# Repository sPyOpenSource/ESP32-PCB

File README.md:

# ESP32-PCBs

Those PCB boards are designed with ESP32. E,g, mini drone, rc car, solar controller, etc.

## Mini Drone Project

It has 4 Motor Controller for Mini Drone with Wireless Connections.

## RC Car Project

2 Motor Controller for RC Car with Wireless Connections. An RC car is a type of remote-controlled vehicle that can be driven by using a radio transmitter or a smartphone app. RC cars can have different sizes, shapes, designs, and features, depending on their purpose and performance. Some RC cars are made for racing, while others are made for off-road, drifting, crawling, or bashing.

## Solar Charger Project

It is the voltage regulator for solar panels for charging and output.

## Goals

The project aims to develop reusable ESP32 PCB designs for:
1. Robotics
2. RC vehicles
3. Drones
4. Solar energy systems
5. Embedded control
6. IoT applications

## License

See the individual project files and repository license for details.

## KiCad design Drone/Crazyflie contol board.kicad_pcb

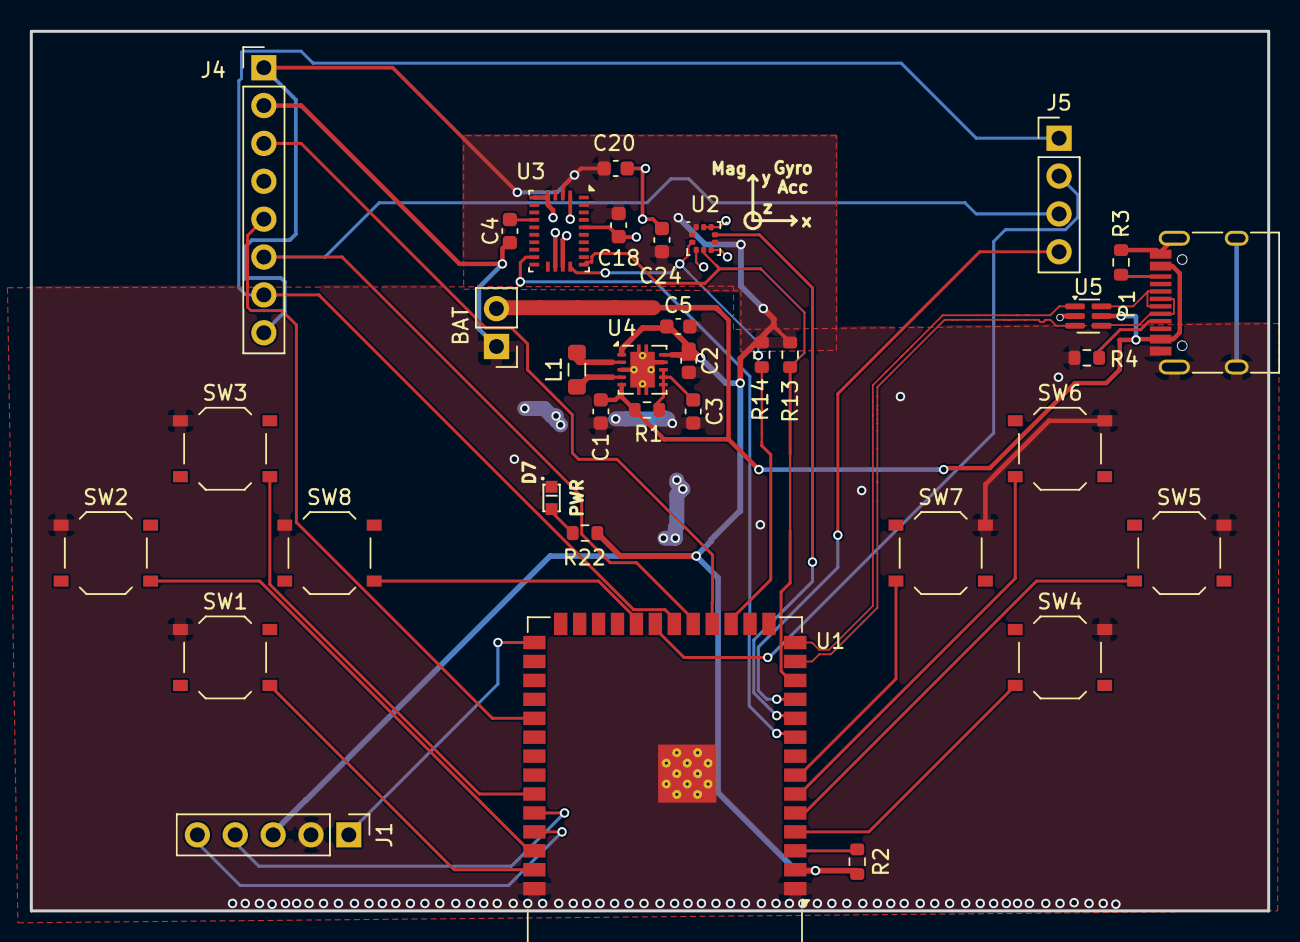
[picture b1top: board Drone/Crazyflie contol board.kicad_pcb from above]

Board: 2 copper layers, 83.0 x 59.0 mm, 35 parts (0 on the bottom side), 34 nets.

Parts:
BAT: Battery; PinHeader_1x02_P2.54mm_Vertical
C1, C2, C5, C18: 10uF; C_0603_1608Metric
C3, C4, C20, C24: 100nF; C_0603_1608Metric
D7: BLUE LED; SMDLED-0603
J1: Conn_01x05_Pin; PinHeader_1x05_P2.54mm_Vertical
J4: Conn_01x08_Pin; PinHeader_1x08_P2.54mm_Vertical
J5: Conn_01x04_Pin; PinHeader_1x04_P2.54mm_Vertical
L1: 2.2uH; L_0805_2012Metric_Pad1.05x1.20mm_HandSolder
P1: USB_C_Plug_USB2.0; USB_C_Receptacle_HRO_TYPE-C-31-M-12
R1: 100R; R_0603_1608Metric
R2: 10k; R_0603_1608Metric
R3, R4: 5.1k; R_0603_1608Metric
R13, R14: 2k2; R_0603_1608Metric
R22: 1k; R_0603_1608Metric
SW1, SW2, SW3, SW4, SW5, SW6, SW7, SW8: SW_Push; SW_Push_1P1T_XKB_TS-1187A
U1: ESP32-S3-WROOM-1
U2: BMP388; ST_HLGA-10_2x2mm_P0.5mm_LayoutBorder3x2y
U3: BNO055; LGA-28_5.2x3.8mm_P0.5mm
U4: TPS63000; Texas_DRC0010J_ThermalVias
U5: NUF2221-Crazyflie-contol-board-rescue; SOT-363_SC-70-6

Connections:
+BATT: BAT.2, C1.1, P1.A4 (VBUS), P1.A9 (VBUS), P1.B4 (VBUS), P1.B9 (VBUS), R1.1, U4.5 (VIN), U5.5 (VBUS)
/CS1: J5.4, U1.11 (IO18)
/CS2: J4.3, U1.18 (IO10)
/DC: J4.5, U1.31 (IO38)
/I2C_SCL: R14.2, U1.17 (IO9), U2.2 (SCK), U3.19 (COM1)
/I2C_SDA: R13.2, U1.12 (IO8), U2.4 (SDI), U3.20 (COM0)
/INT1: U1.9 (IO16), U3.14 (INT)
/MISO: J5.2, U1.21 (IO13)
/MOSI: J4.6, J5.3, U1.19 (IO11)
/RX: J1.4, U1.36 (RXD0)
/SCK: J4.7, J5.1, U1.20 (IO12)
/SW3: SW3.2, U1.35 (IO42)
/TX: J1.5, U1.37 (TXD0)
/USBD+: P1.A6 (D+), P1.B6, U1.14 (USB_D+), U5.1 (D1I), U5.6 (D1C)
/USBD-: P1.A7 (D-), P1.B7, U1.13 (USB_D-), U5.3 (D2I), U5.4 (D2C)
GND: BAT.1, C1.2, C2.2, C3.2, C4.2, C5.2, C18.2, C20.2, C24.2, D7.2 (K), J1.2, J4.2, P1.A1 (GND), P1.A12 (GND), P1.B1 (GND), P1.B12 (GND), P1.S1 (SHIELD), R3.2, R4.1, SW1.1, SW2.1, SW3.1, SW4.1, SW5.1, SW6.1, SW7.1, SW8.1, U1.1 (GND), U1.40 (GND), U1.41 (GND), U2.3 (GND), U2.5 (SDO), U2.8 (GND), U2.9 (GND), U3.2 (GND), U3.5 (PS1), U3.6 (PS0), U3.17 (COM3), U3.18 (COM2), U3.25 (GNDIO), U4.3 (PGND), U4.9 (GND), U4.11 (PGND), U5.2 (GND)
INT0: J1.1, U1.27 (IO0)
INT2: U1.10 (IO17), U2.7 (INT)
unnamed: D7.1 (A), R22.1
unnamed: P1.A5 (CC), R4.2
unnamed: P1.B5 (VCONN), R3.1
unnamed: R2.2, U1.3 (EN)
unnamed: SW1.2, U1.39 (IO1)
unnamed: SW2.2, U1.38 (IO2)
unnamed: SW4.2, U1.4 (IO4)
unnamed: SW5.2, U1.5 (IO5)
unnamed: SW6.2, U1.6 (IO6)
unnamed: SW7.2, U1.7 (IO7)
unnamed: SW8.2, U1.22 (IO14)
unnamed: C4.1, U3.9 (CAP)
unnamed: C3.1, R1.2, U4.6 (EN), U4.7 (PS/SYNC), U4.8 (VINA)
unnamed: L1.1, U4.4 (L1)
unnamed: L1.2, U4.2 (L2)
VCC: C2.1, C5.1, C18.1, C20.1, C24.1, J1.3, J4.1, J4.8, R2.1, R13.1, R14.1, R22.2, U1.2 (3V3), U2.1 (VDDIO), U2.6 (CSB), U2.10 (VDD), U3.3 (VDD), U3.4 (~BOOT_LOAD_PIN), U3.28 (VDDIO), U4.1 (VOUT), U4.10 (FB)

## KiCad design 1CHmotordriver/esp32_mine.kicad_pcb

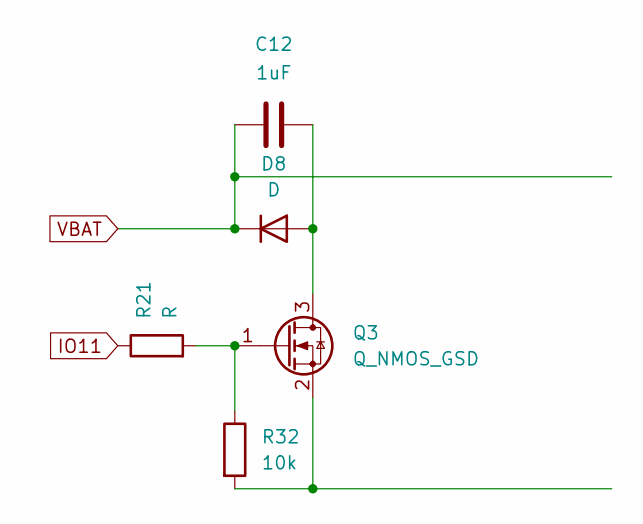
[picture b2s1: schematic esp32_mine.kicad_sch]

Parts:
C12: 1uF; C_0603_1608Metric
D8: D
Q3: Q_NMOS_GSD
R21: R; R_0402_1005Metric
R32: 10k; R_0402_1005Metric

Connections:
IO11: R21.1
unnamed: C12.2, D8.2 (A), Q3.3 (D)
unnamed: Q3.1 (G), R21.2, R32.1
unnamed: Q3.2 (S), R32.2
VBAT: C12.1, D8.1 (K)

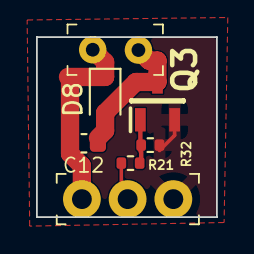
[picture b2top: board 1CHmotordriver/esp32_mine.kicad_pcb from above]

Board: 4 copper layers, 10.0 x 10.0 mm, 5 parts (0 on the bottom side), 4 nets.

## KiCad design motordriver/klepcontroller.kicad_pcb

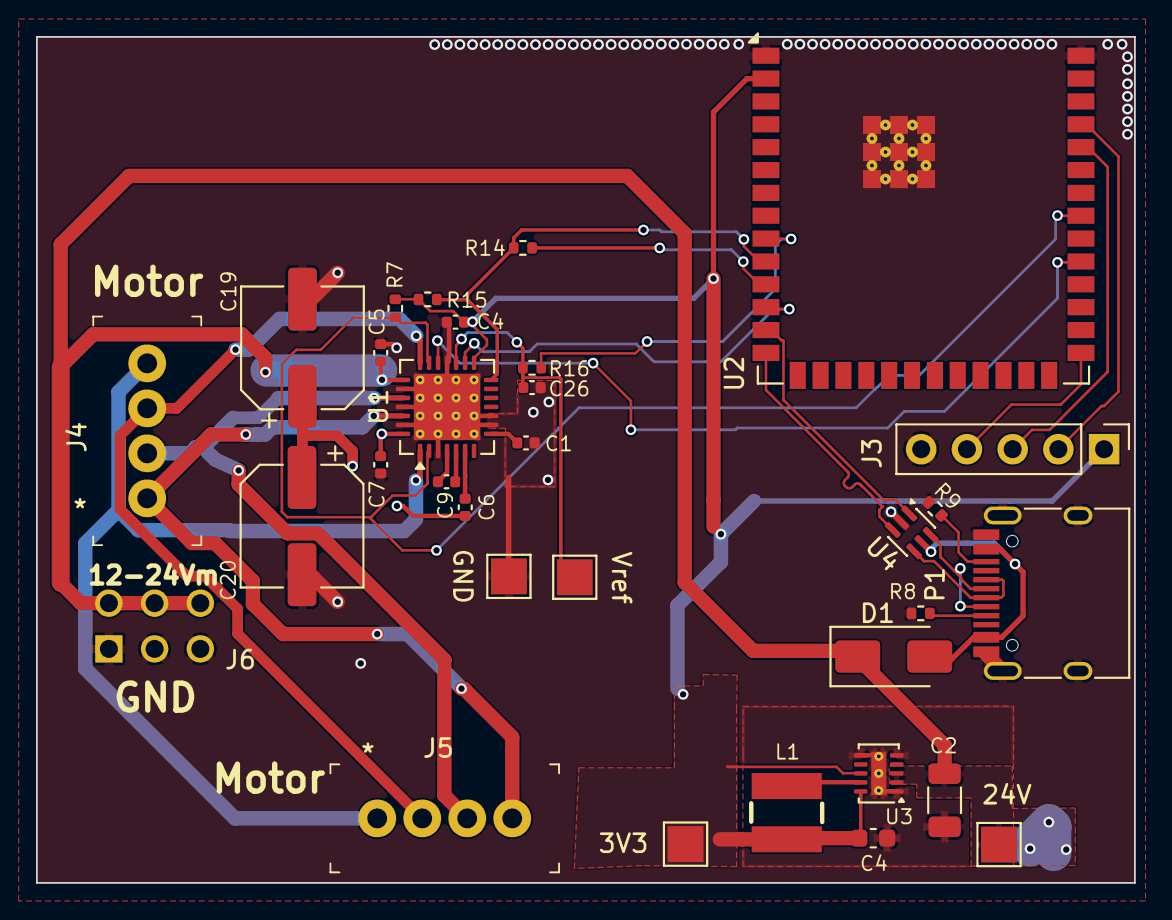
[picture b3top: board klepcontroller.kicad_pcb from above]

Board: 4 copper layers, 61.0 x 47.0 mm, 32 parts (0 on the bottom side), 27 nets.

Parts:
C1: 2.2uF; C_0402_1005Metric
C2: 2.2uF; C_1206_3216Metric
C4: 22uF; C_0402_1005Metric
C4#2: 22u; C_0603_1608Metric
C5, C26: 100n; C_0402_1005Metric
C6, C7: 100nF; C_0402_1005Metric
C9: 22n; C_0402_1005Metric
C19, C20: 47uF; CP_Elec_6.3x5.8
D1: SS14; D_SMA
J3: SPI; PinHeader_1x05_P2.54mm_Vertical
J4, J5: Motor; PinHeader_1x4_P2.5mm_Drill1.1mm
J6: Power; 2x3_SPI_header
L1: 10uH; IND-SMD_L3.9-W3.9-1
P1: USB_C_Plug_USB2.0; USB_C_Receptacle_HRO_TYPE-C-31-M-12
R7: 10k; R_0402_1005Metric
R8, R9: 5k1; R_0402_1005Metric
R14, R16: 1K; R_0402_1005Metric
R15: 10K; R_0402_1005Metric
TP1: +3V3; TestPoint_Pad_2.0x2.0mm
TP2: GND; TestPoint_Pad_2.0x2.0mm
TP3: +24V; TestPoint_Pad_2.0x2.0mm
TP5: Vref; TestPoint_Pad_2.0x2.0mm
U1: TMC2209-LA; VQFN-28-1EP_5x5mm_P0.5mm_EP3.7x3.7mm_ThermalVias
U2: ESP32-S3-WROOM-2
U3: TPS62177DQC; WSON-10-1EP_2x3mm_P0.5mm_EP0.84x2.4mm_ThermalVias
U4: SOT-363_SC-70-6

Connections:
5V: C1.1, U1.8 (5VOUT)
+3V3: C4.1, C4#2.1, J3.1, L1.2, R7.1, R15.1, TP1.1 (1_1), U1.15 (VCC_IO), U2.2 (3V3), U3.8 (~SLEEP), U3.10 (VOS)
+5V: D1.2 (A), P1.A4 (VBUS), P1.A9 (VBUS), P1.B4 (VBUS), P1.B9 (VBUS), U4.5
+24V: C2.1, C5.2, C6.2, C7.2, C19.1, C20.1, D1.1 (K), J6.2, J6.4, J6.6, TP3.1 (1_1), U1.22 (VS), U1.28 (VS), U3.2 (VIN), U3.3 (EN)
/pusher/M_PWM: R16.1, U2.9 (IO16)
/pusher/M_UART: R14.2, R15.2, U1.14 (~PD/UART), U2.10 (IO17)
/pusher/Vref: C26.2, R16.2, TP5.1 (1_1), U1.17 (VREF)
A1: J4.2, J5.3, U1.24 (OA1)
A2: J4.3, J5.2, U1.21 (OA2)
B1: J4.1, J5.4, U1.26 (OB1)
B2: J4.4, J5.1, U1.1 (OB2)
DIRECTION: U1.19 (DIR), U2.31 (IO38)
ENABLE: R7.2, U1.2 (~EN), U1.20 (STDBY), U2.33 (MTDO/IO40)
GND: C1.2, C2.2, C4.2, C4#2.2, C5.1, C7.1, C19.2, C20.2, C26.1, J3.5, J6.1, J6.3, J6.5, P1.A1 (GND), P1.A12 (GND), P1.B1 (GND), P1.B12 (GND), P1.S1 (SHIELD), R8.1, R9.1, TP2.1 (1_1), U1.3 (GND), U1.9 (MS1/AD0), U1.10 (MS2/AD1), U1.18 (GND), U1.23 (BRA), U1.25 (NC), U1.27 (BRB), U1.29 (GND), U2.1 (GND), U2.40 (GND), U2.41 (GND), U3.1 (PGND), U3.5 (FB), U3.6 (AGND), U3.11 (PAD), U4.2
GPIO0: J3.4, U2.27 (IO0)
unnamed: P1.A5 (CC), R8.2
unnamed: P1.A6 (D+), P1.B6, U2.14 (USB_D+/IO20), U4.3, U4.4
unnamed: P1.A7 (D-), P1.B7, U2.13 (USB_D-/IO19), U4.1, U4.6
unnamed: P1.B5 (VCONN), R9.2
unnamed: C9.1, U1.5 (CPI)
unnamed: C9.2, U1.4 (CPO)
unnamed: C6.1, U1.6 (VCP)
unnamed: L1.1, U3.9 (SW)
Rx: J3.3, U2.36 (RXD0/IO44)
SDO: R14.1, U2.11 (IO18)
STEP: U1.16 (STEP), U2.12 (IO8)
Tx: J3.2, U2.37 (TXD0/IO43)

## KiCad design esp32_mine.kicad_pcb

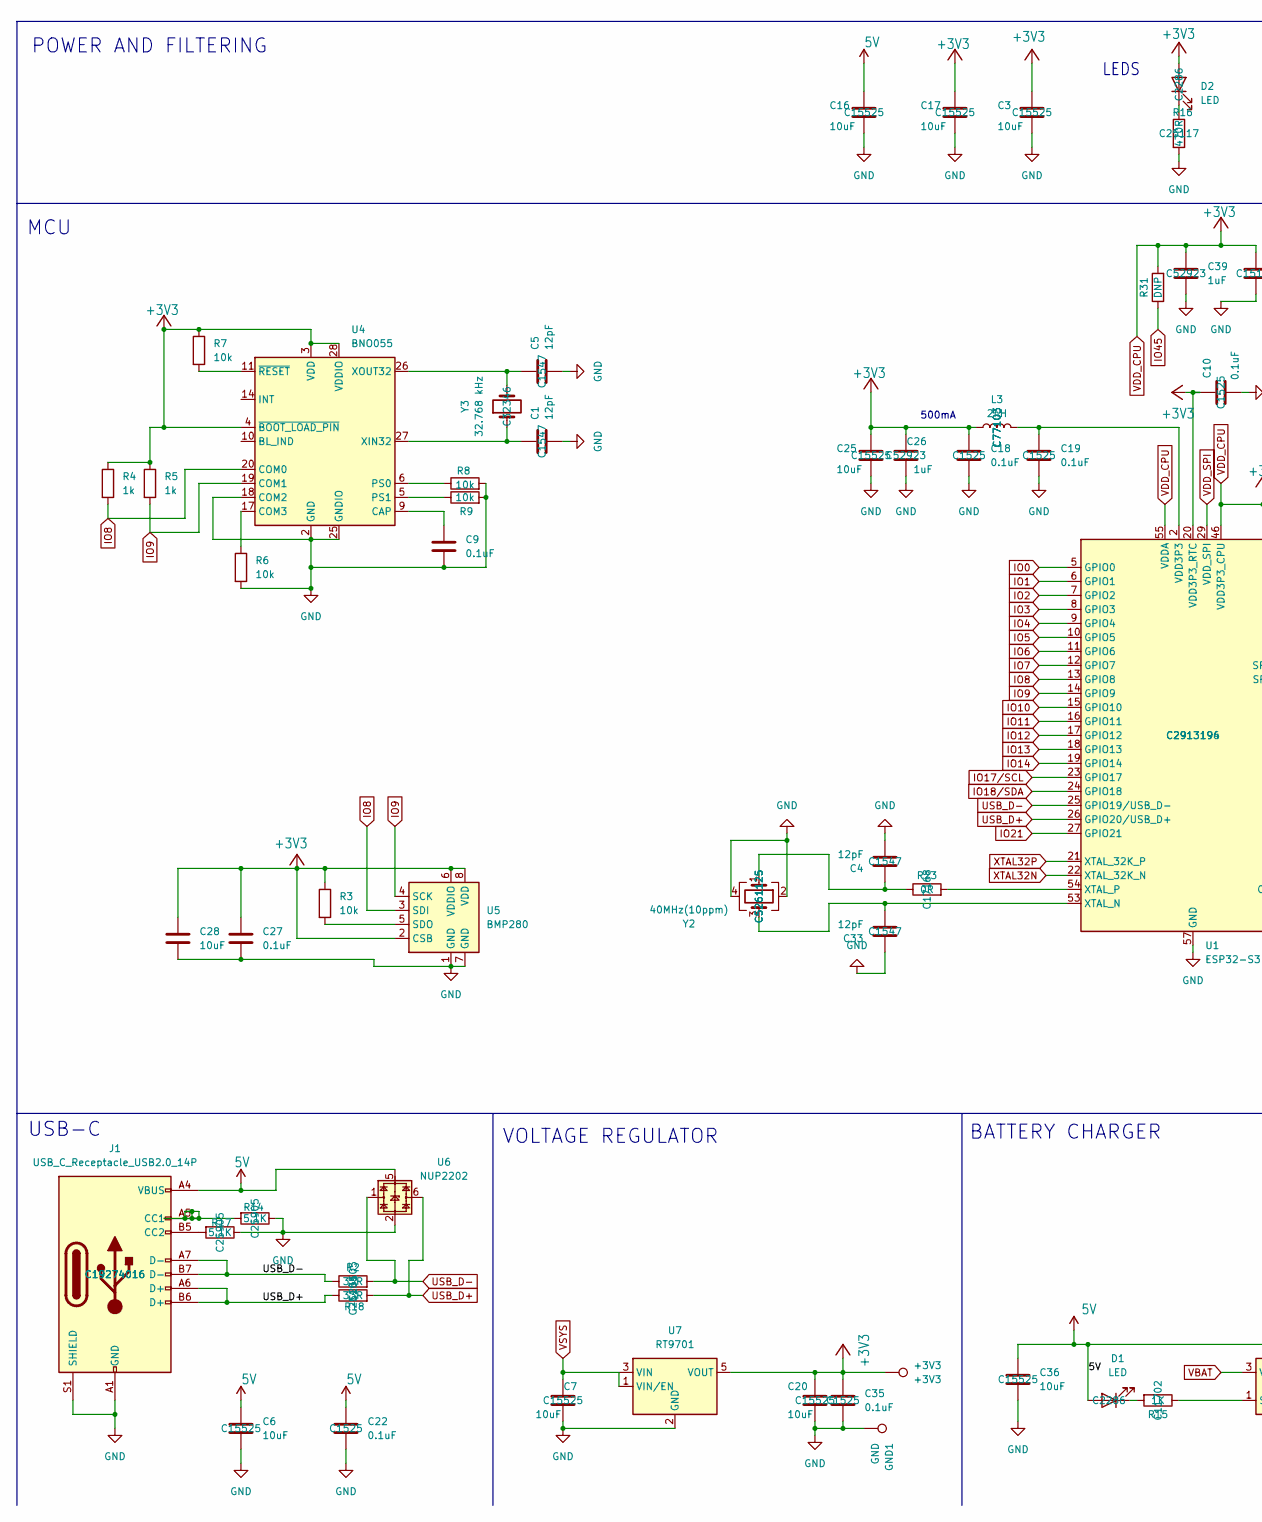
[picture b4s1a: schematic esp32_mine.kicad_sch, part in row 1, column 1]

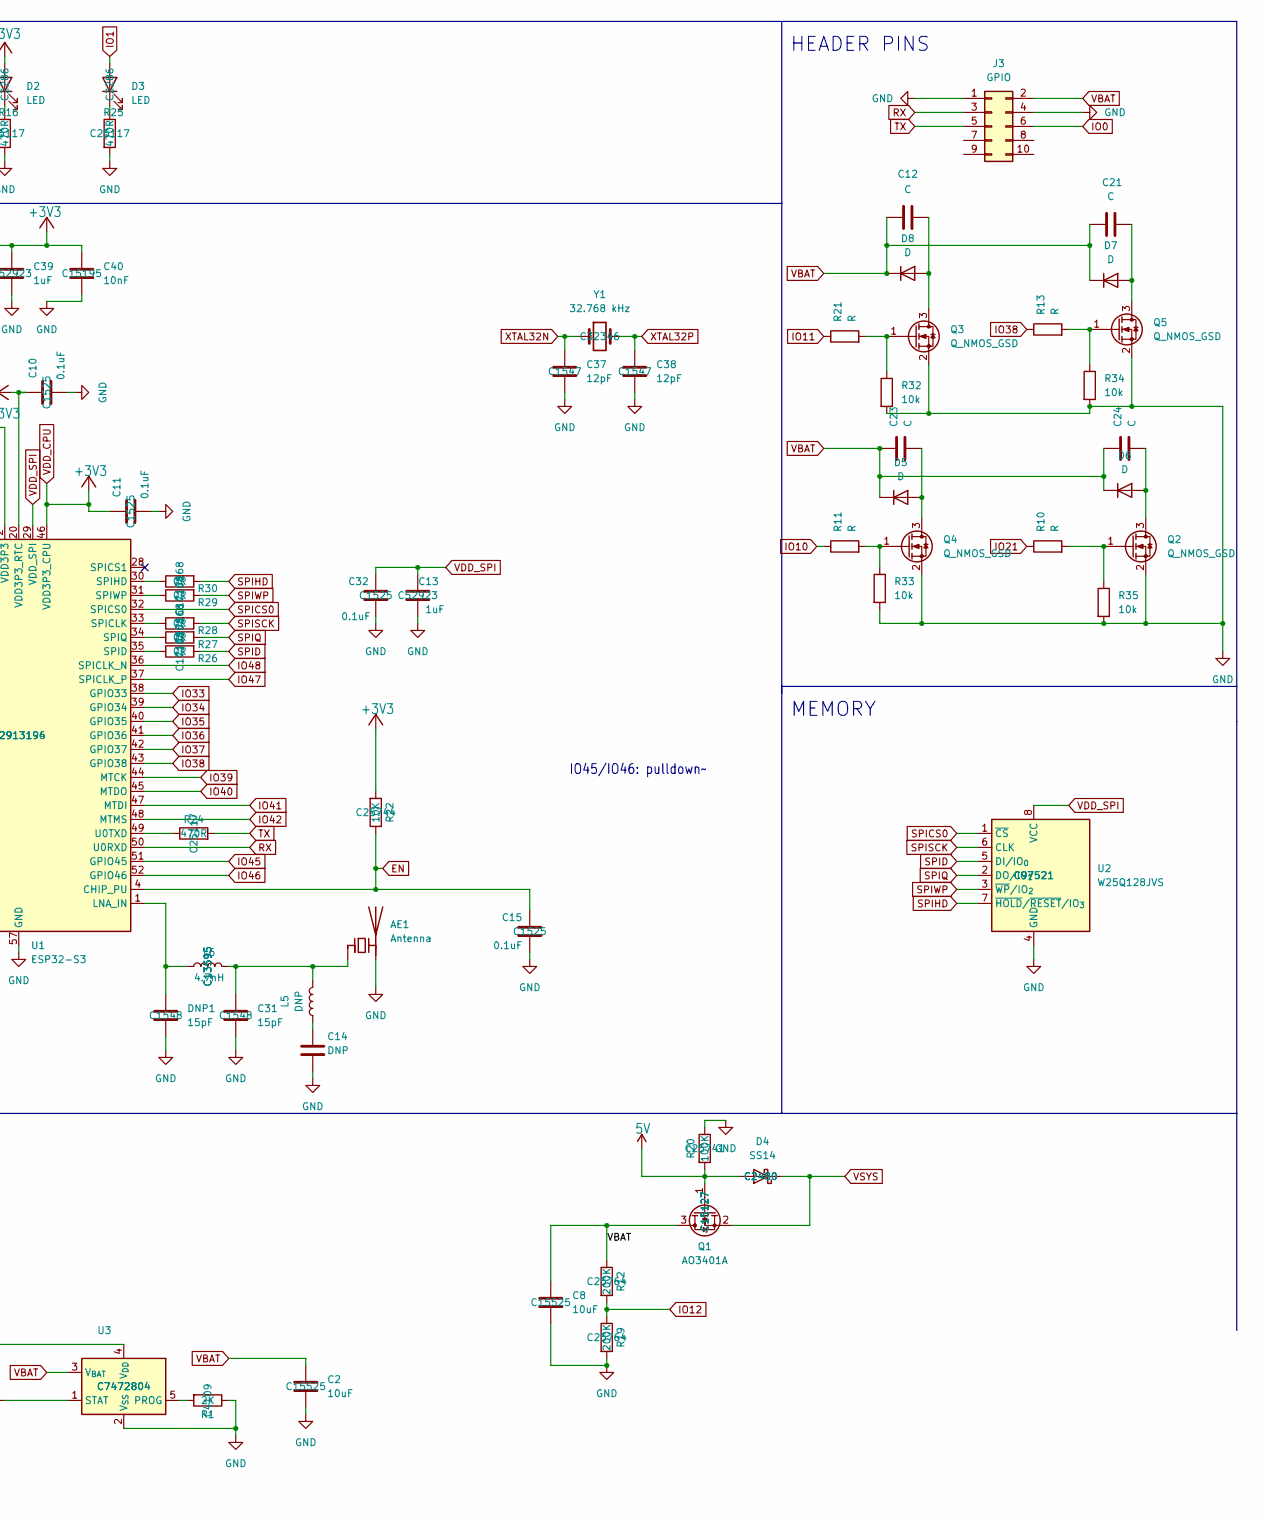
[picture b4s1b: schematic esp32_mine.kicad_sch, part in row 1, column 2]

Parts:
+3V3: +3V3; TestPoint_Pad_D1.0mm
AE1: Antenna; Texas_SWRA117D_2.4GHz_Left
C1, C4, C5, C33, C37, C38: 12pF; C_0402_1005Metric; MNF PART NUMBER C1547; LCSC C1547
C2, C3, C6, C7, C8, C16, C17, C20, C25, C36: 10uF; C_0402_1005Metric; MNF PART NUMBER C15525; LCSC C15525
C9, C27: 0.1uF; C_0603_1608Metric
C10, C11, C15, C18, C19, C22, C32, C35: 0.1uF; C_0402_1005Metric; MNF PART NUMBER C1525; LCSC C1525
C12, C21, C23, C24: C; C_0603_1608Metric
C13, C26, C39: 1uF; C_0402_1005Metric; MNF PART NUMBER C52923; LCSC C52923
C14: DNP; C_0402_1005Metric
C28: 10uF; C_0603_1608Metric
C31: 15pF; C_0402_1005Metric; MNF PART NUMBER C1548; LCSC C1548
C40: 10nF; C_0402_1005Metric; MNF PART NUMBER C15195; LCSC C15195
D1, D2, D3: LED; LED_0603_1608Metric; MNF PART NUMBER C2286; LCSC C2286
D4: SS14; D_SMA; MNF PART NUMBER C2480; LCSC C2480
D5, D6, D7, D8: D
DNP1: 15pF; C_0402_1005Metric; MNF PART NUMBER C1548; LCSC C1548
GND1: GND; TestPoint_Pad_D1.0mm
J1: USB_C_Receptacle_USB2.0_14P; USB_C_Receptacle_HCTL_HC-TYPE-C-16P-01A; MNF PART NUMBER C19274016; LCSC C19274016
J3: GPIO; PinHeader_2x05_P2.54mm_Vertical
L3: 2nH; L_0402_1005Metric; MNF PART NUMBER C77103; LCSC C77103
L5: DNP; L_0402_1005Metric
L6: 4.7nH; L_0402_1005Metric; MNF PART NUMBER C13595; LCSC C13595
Q1: AO3401A; SOT-23; MNF PART NUMBER C15127; LCSC C15127
Q2, Q3, Q4, Q5: Q_NMOS_GSD
R1: 2K; R_0402_1005Metric; MNF PART NUMBER C4109; LCSC C4109
R2, R18: 33R; R_0402_1005Metric; MNF PART NUMBER C25105; LCSC C25105
R3, R6, R7, R8, R9, R32, R33, R34, R35: 10k; R_0402_1005Metric
R4, R5: 1k; R_0402_1005Metric
R10, R11, R13, R21: R; R_0402_1005Metric
R12, R19: 200K; R_0402_1005Metric; MNF PART NUMBER C25764; LCSC C25764
R14, R17: 5.1K; R_0402_1005Metric; MNF PART NUMBER C25905; LCSC C25905
R15: 1K; R_0402_1005Metric; MNF PART NUMBER C11702; LCSC C11702
R16, R24, R25: 470R; R_0402_1005Metric; MNF PART NUMBER C25117; LCSC C25117
R20: 100K; R_0402_1005Metric; MNF PART NUMBER C25741; LCSC C25741
R22: 10K; R_0402_1005Metric; MNF PART NUMBER C25744; LCSC C25744
R23, R26, R27, R28, R29, R30: 0R; R_0402_1005Metric; MNF PART NUMBER C17168; LCSC C17168
R31: DNP; R_0402_1005Metric
U1: ESP32-S3; QFN-56-1EP_7x7mm_P0.4mm_EP4x4mm; MNF PART NUMBER C2913196; LCSC C2913194
U2: W25Q128JVS; SOIC-8_5.3x5.3mm_P1.27mm; MNF PART NUMBER C97521; LCSC C97521
U3: MCP73831-2-OT; SOT-23-5; MNF PART NUMBER C7472804; LCSC C7472804
U4: BNO055; LGA-28_5.2x3.8mm_P0.5mm
U5: BMP280; Bosch_LGA-8_2x2.5mm_P0.65mm_ClockwisePinNumbering
U6: NUP2202; SOT-363_SC-70-6
U7: RT9701
Y1, Y3: 32.768 kHz; Crystal_SMD_3215-2Pin_3.2x1.5mm; MNF PART NUMBER C32346; LCSC C32346
Y2: 40MHz(10ppm); Crystal_SMD_2520-4Pin_2.5x2.0mm; MNF PART NUMBER C5261125; LCSC C5261125

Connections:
5V: C6.1, C16.1, C22.1, C36.1, D1.2 (A), D4.2 (A), J1.A4 (VBUS), J1.A9 (VBUS), J1.B4 (VBUS), J1.B9 (VBUS), Q1.1 (G), R20.2, U3.4 (V_{DD}), U6.5
EN: C15.1, R22.1, U1.4 (CHIP_PU)
GND: AE1.2 (PCB_Trace), C1.2, C2.2, C3.2, C4.2, C5.2, C6.2, C7.2, C8.2, C9.2, C10.2, C11.2, C13.2, C14.2, C15.2, C16.2, C17.2, C18.2, C19.2, C20.2, C22.2, C25.2, C26.2, C27.2, C28.2, C31.2, C32.2, C33.1, C35.2, C36.2, C37.2, C38.2, C39.2, C40.2, DNP1.2, GND1.1, J1.A1 (GND), J1.A12 (GND), J1.B1 (GND), J1.B12 (GND), J1.S1 (SHIELD), J3.1, J3.4, Q2.2 (S), Q3.2 (S), Q4.2 (S), Q5.2 (S), R1.1, R6.2, R8.2, R9.2, R14.1, R16.2, R17.1, R19.2, R20.1, R25.2, R32.2, R33.2, R34.2, R35.2, U1.57 (GND), U2.4 (GND), U3.2 (V_{SS}), U4.2 (GND), U4.18 (COM2), U4.25 (GNDIO), U5.1 (GND), U5.7 (GND), U6.2, U7.2 (GND), Y2.2, Y2.4
IO0: J3.6, U1.5 (GPIO0)
IO1: D3.2 (A), U1.6 (GPIO1)
IO2: U1.7 (GPIO2)
IO3: U1.8 (GPIO3)
IO4: U1.9 (GPIO4)
IO5: U1.10 (GPIO5)
IO6: U1.11 (GPIO6)
IO7: U1.12 (GPIO7)
IO8: R4.2, U1.13 (GPIO8), U4.20 (COM0), U5.3 (SDI)
IO9: R5.2, U1.14 (GPIO9), U4.19 (COM1), U5.4 (SCK)
IO10: R11.1, U1.15 (GPIO10)
IO11: R21.1, U1.16 (GPIO11)
IO12: R12.2, R19.1, U1.17 (GPIO12)
IO13: U1.18 (GPIO13)
IO14: U1.19 (GPIO14)
IO17/SCL: U1.23 (GPIO17)
IO18/SDA: U1.24 (GPIO18)
IO21: R10.1, U1.27 (GPIO21)
IO33: U1.38 (GPIO33)
IO34: U1.39 (GPIO34)
IO35: U1.40 (GPIO35)
IO36: U1.41 (GPIO36)
IO37: U1.42 (GPIO37)
IO38: R13.1, U1.43 (GPIO38)
IO39: U1.44 (MTCK)
IO40: U1.45 (MTDO)
IO41: U1.47 (MTDI)
IO42: U1.48 (MTMS)
IO45: R31.1, U1.51 (GPIO45)
IO46: U1.52 (GPIO46)
IO47: U1.37 (SPICLK_P)
IO48: U1.36 (SPICLK_N)
unnamed: AE1.1 (FEED), C31.1, L5.2, L6.2
unnamed: C4.1, R23.1, Y2.1
unnamed: C14.1, L5.1
unnamed: C19.1, L3.2, U1.2 (VDD3P3), U1.3 (VDD3P3)
unnamed: D1.1 (K), R15.2
unnamed: D2.1 (K), R16.1
unnamed: D3.1 (K), R25.1
unnamed 42: C23.2, D5.2 (A), Q4.3 (D); also elsewhere on the board
unnamed 43: C24.2, D6.2 (A), Q2.3 (D); also elsewhere on the board
unnamed 44: C21.2, D7.2 (A), Q5.3 (D); also elsewhere on the board
unnamed 45: C12.2, D8.2 (A), Q3.3 (D); also elsewhere on the board
unnamed: J1.A5 (CC1), R14.2
unnamed: J1.B5 (CC2), R17.2
unnamed: Q2.1 (G), R10.2, R35.1
unnamed: Q3.1 (G), R21.2, R32.1
unnamed: Q4.1 (G), R11.2, R33.1
unnamed: Q5.1 (G), R13.2, R34.1
unnamed: DNP1.1, L6.1, U1.1 (LNA_IN)
unnamed: R28.1, U1.33 (SPICLK)
unnamed: R26.1, U1.35 (SPID)
unnamed: R30.1, U1.30 (SPIHD)
unnamed: R27.1, U1.34 (SPIQ)
unnamed: R29.1, U1.31 (SPIWP)
unnamed: R24.1, U1.49 (U0TXD)
unnamed: C33.2, U1.53 (XTAL_N), Y2.3
unnamed: R23.2, U1.54 (XTAL_P)
unnamed: R1.2, U3.5 (PROG)
unnamed: R15.1, U3.1 (STAT)
unnamed: C9.1, U4.9 (CAP)
unnamed: R6.1, U4.17 (COM3)
unnamed: R8.1, U4.6 (PS0)
unnamed: R9.1, U4.5 (PS1)
unnamed: C1.1, U4.27 (XIN32), Y3.1
unnamed: C5.1, U4.26 (XOUT32), Y3.2
unnamed: R7.2, U4.11 (~RESET)
unnamed: R3.2, U5.5 (SDO)
RX: J3.3, U1.50 (U0RXD)
SPICS0: U1.32 (SPICS0), U2.1 (~CS)
SPID: R26.2, U2.5 (DI/IO_{0})
SPIHD: R30.2, U2.7 (~HOLD/~RESET/IO_{3})
SPIQ: R27.2, U2.2 (DO/IO_{1})
SPISCK: R28.2, U2.6 (CLK)
SPIWP: R29.2, U2.3 (~WP/IO_{2})
TX: J3.5, R24.2
USB_D+: J1.A6 (D+), J1.B6 (D+), R18.1, R18.2, U1.26 (GPIO20/USB_D+), U6.6
USB_D-: J1.A7 (D-), J1.B7 (D-), R2.1, R2.2, U1.25 (GPIO19/USB_D-), U6.1
VBAT: C2.1, C8.1, C12.1, C21.1, C23.1, C24.1, D5.1 (K), D6.1 (K), D7.1 (K), D8.1 (K), J3.2, Q1.3 (D), R12.1, U3.3 (V_{BAT}); also elsewhere on the board
VDD_CPU: +3V3.1, C3.1, C10.1, C11.1, C17.1, C18.1, C20.1, C25.1, C26.1, C27.1, C28.1, C35.1, C39.1, C40.1, D2.2 (A), L3.1, R3.1, R4.1, R5.1, R7.1, R22.2, R31.2, U1.20 (VDD3P3_RTC), U1.46 (VDD3P3_CPU), U1.55 (VDDA), U1.56 (VDDA), U4.3 (VDD), U4.4 (~BOOT_LOAD_PIN), U4.28 (VDDIO), U5.2 (CSB), U5.6 (VDDIO), U5.8 (VDD), U7.5 (VOUT)
VDD_SPI: C13.1, C32.1, U1.29 (VDD_SPI), U2.8 (VCC)
VSYS: C7.1, D4.1 (K), Q1.2 (S), U7.1 (VIN/EN), U7.3 (VIN)
XTAL32N: C37.1, U1.22 (XTAL_32K_N), Y1.1
XTAL32P: C38.1, U1.21 (XTAL_32K_P), Y1.2

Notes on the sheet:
BATTERY CHARGER
VOLTAGE REGULATOR
500mA
LEDS
MCU
HEADER PINS
MEMORY
POWER AND FILTERING
IO45/IO46: pulldown~~{}
USB-C

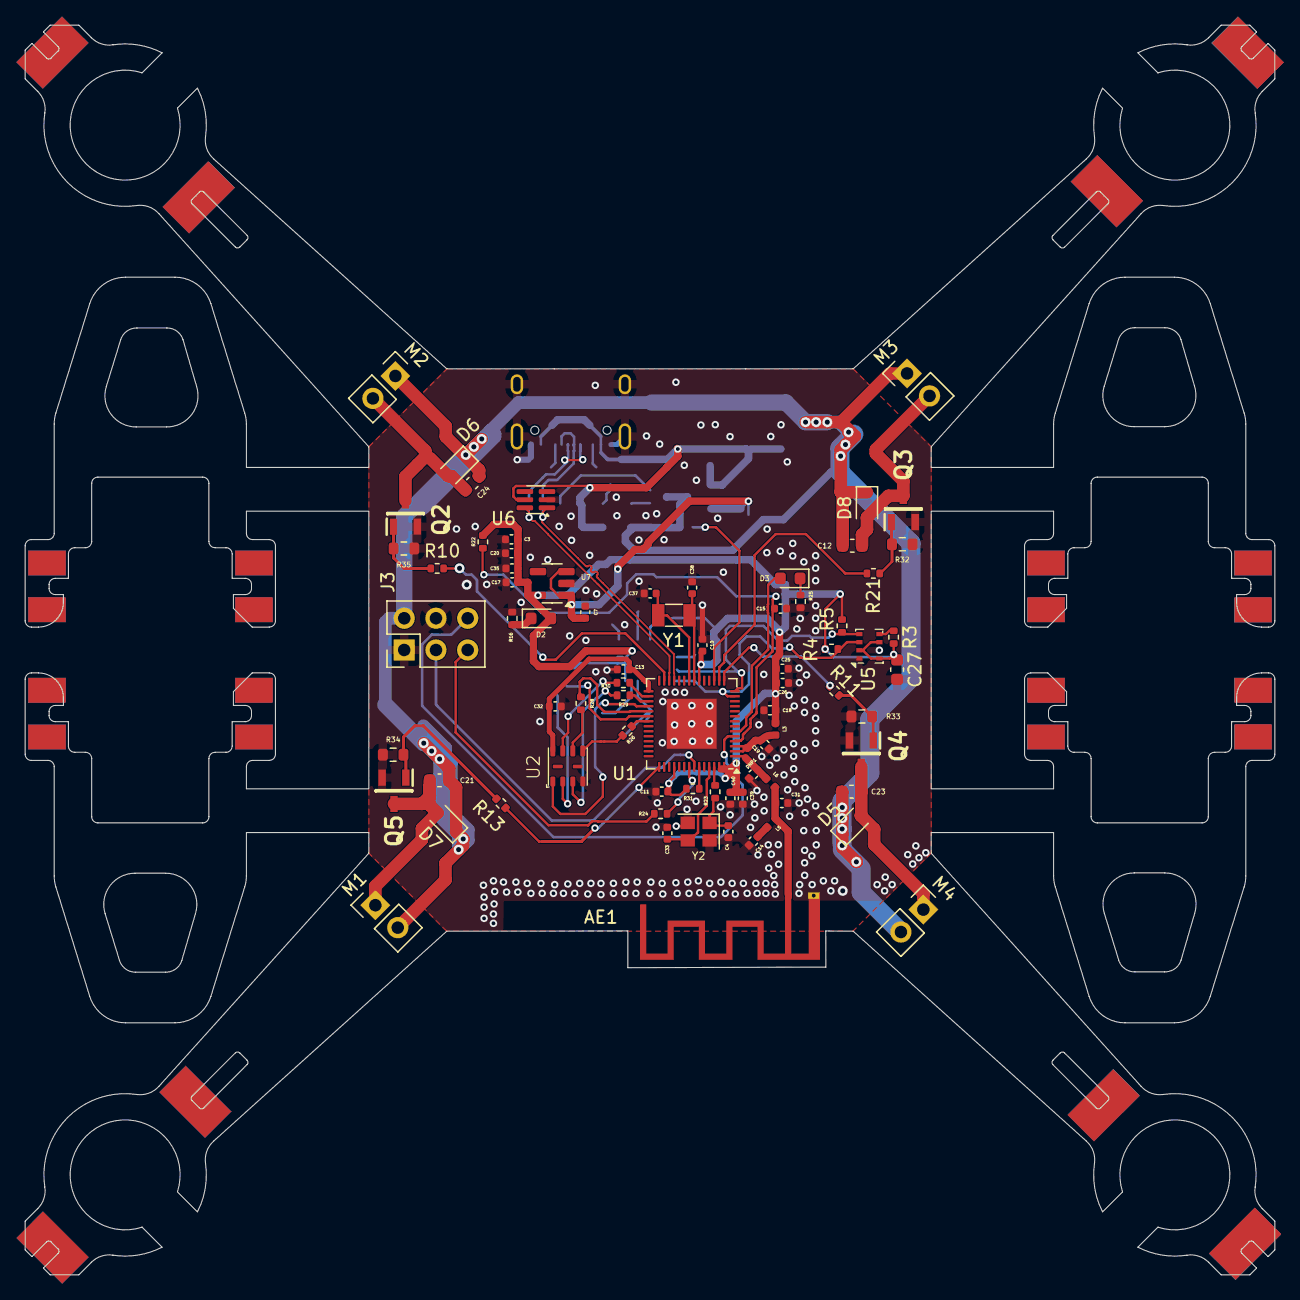
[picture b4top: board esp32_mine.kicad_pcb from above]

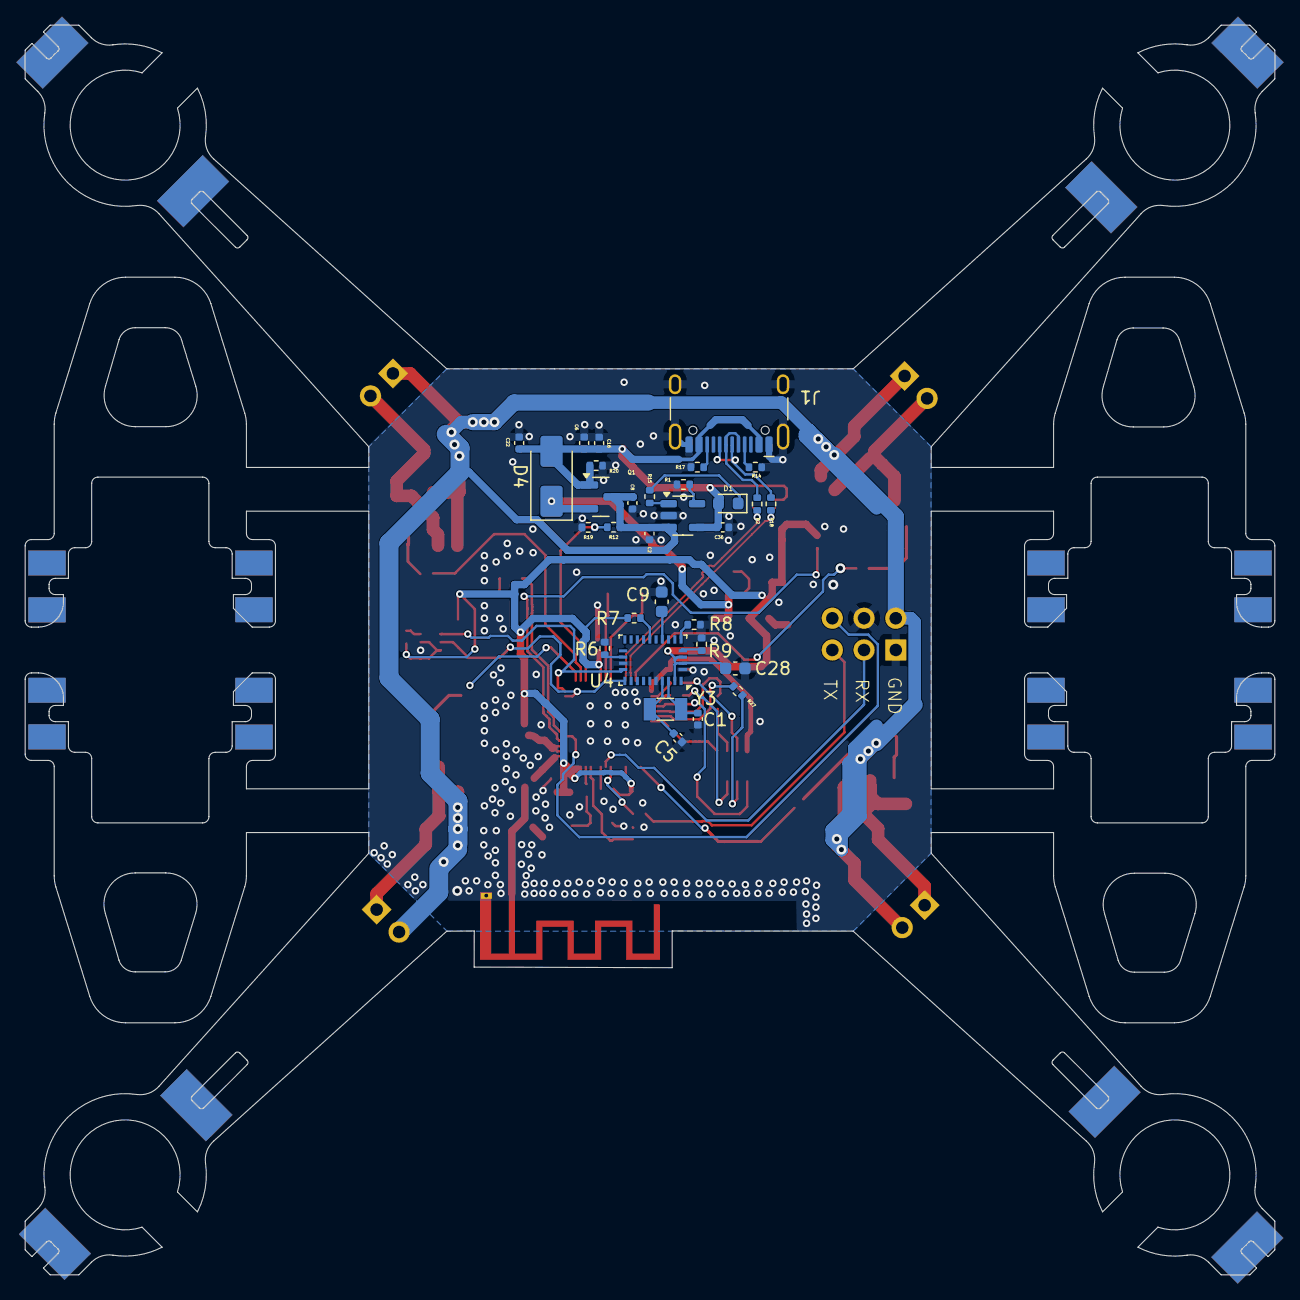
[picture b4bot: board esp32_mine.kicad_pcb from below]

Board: 4 copper layers, 100.0 x 100.0 mm, 106 parts (31 on the bottom side), 65 nets.

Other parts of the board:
M1, M2, M3, M4: PinHeader_1x02_P2.54mm_Vertical

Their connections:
unnamed 42: M4.1; also elsewhere on the board
unnamed 43: M2.2; also elsewhere on the board
unnamed 44: M1.1; also elsewhere on the board
unnamed 45: M3.2; also elsewhere on the board
VBAT: M1.2, M2.1, M3.1, M4.2; also elsewhere on the board

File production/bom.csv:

"Designator","Footprint","Quantity","Value","LCSC Part #"
"C10, C11, C15, C18, C19, C22, C32, C35","SMD0402",8,"0.1uF",
"C13, C26, C39","SMD0402",3,"1uF",
"C16, C17, C2, C20, C25, C3, C36, C6, C7, C8","SMD0402",10,"10uF",
"C31, DNP1","SMD0402",2,"15pF",
"C33, C37, C38, C4, C1, C5","SMD0402",4,"12pF",
"C40","SMD0402",1,"10nF",
"D1, D2, D3","SMD0603",3,"LED",
"D4","D_SMA",1,"SS14",
"J1","USB_C_Receptacle_HCTL_HC-TYPE-C-16P-01A",1,"USB_C_Receptacle_USB2.0_14P",
"J3","PinHeader_1x18_P2.54mm_Vertical",2,"Conn_01x18_Pin",
"L3","SMD0402",1,"2nH",
"L6","SMD0402",1,"4.7nH",
"Q1","SOT-23",1,"AO3401A",
"R1","SMD0402",1,"2K",
"R12, R19","SMD0402",2,"200K",
"R14, R17","SMD0402",2,"5.1K",
"R15","SMD0402",1,"1K",
"R16, R24, R25","SMD0402",3,"470R",
"R18, R2","SMD0402",2,"33R",
"R20","SMD0402",1,"100K",
"R21, R13, R11, R10","SMD0402",4,"100R",
"R23, R26, R27, R28, R29, R30","SMD0402",6,"0R",
"U1","QFN-56-1EP_7x7mm_P0.4mm_EP4x4mm",1,"ESP32-S3",
"U2","SOIC-8_5.3x5.3mm_P1.27mm",1,"W25Q128JVS",
"U3","SOT-23-5",1,"MCP73831-2-OT",
"U4","SOT-223-3_TabPin2",1,"BNO055",
"Y1,Y3","Crystal_SMD_3215-2Pin_3.2x1.5mm",1,"32.768 kHz",
"Y2","Crystal_SMD_2520-4Pin_2.5x2.0mm",1,"40MHz(10ppm)",
"U5",,1,"BMP280",
"U7",,1,"RT9080-33GJ5",
"D5,D6,D7,D8",,4,,
"R22, R4","SMD0402",2,"10K",
"R33, R35, R32, R34","SMD0603",4,"10K",
"C9,C27","SMD0603",1,"0.1uF",
"C28","SMD0603",1,"10uF",

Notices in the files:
Drone/IMU.kicad_sch:
Bitcraze AB (CC BY-NC-SA)
